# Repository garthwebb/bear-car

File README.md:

# Bear Car

Bear car is an art car project brought to Burning Man in 2015 ([photos](https://photos.app.goo.gl/hQNxJEHgqHZzFq1y2)), meant to look like
[rilakkuma](http://www.san-x.jp/characters/rilakkuma.html), the lazy bear.

It consists of two Huffy beach cruiser bikes that are bolted together.
A linkage in front connects the two bicycles steering columns in an Ackermann steering geometry.  The bicycles are driven by two 350W electric
motors via a chain to the rear wheels.  Two people can ride in the car, who's top speed is around 15mph and can drive for around 2 hours on a charge.

An LED controller connects to a WiFi router that allows an iPhone running [L.E.D Labs](https://apps.apple.com/us/app/l-e-d-lab/id832042156)
to connect and control the dome lights.

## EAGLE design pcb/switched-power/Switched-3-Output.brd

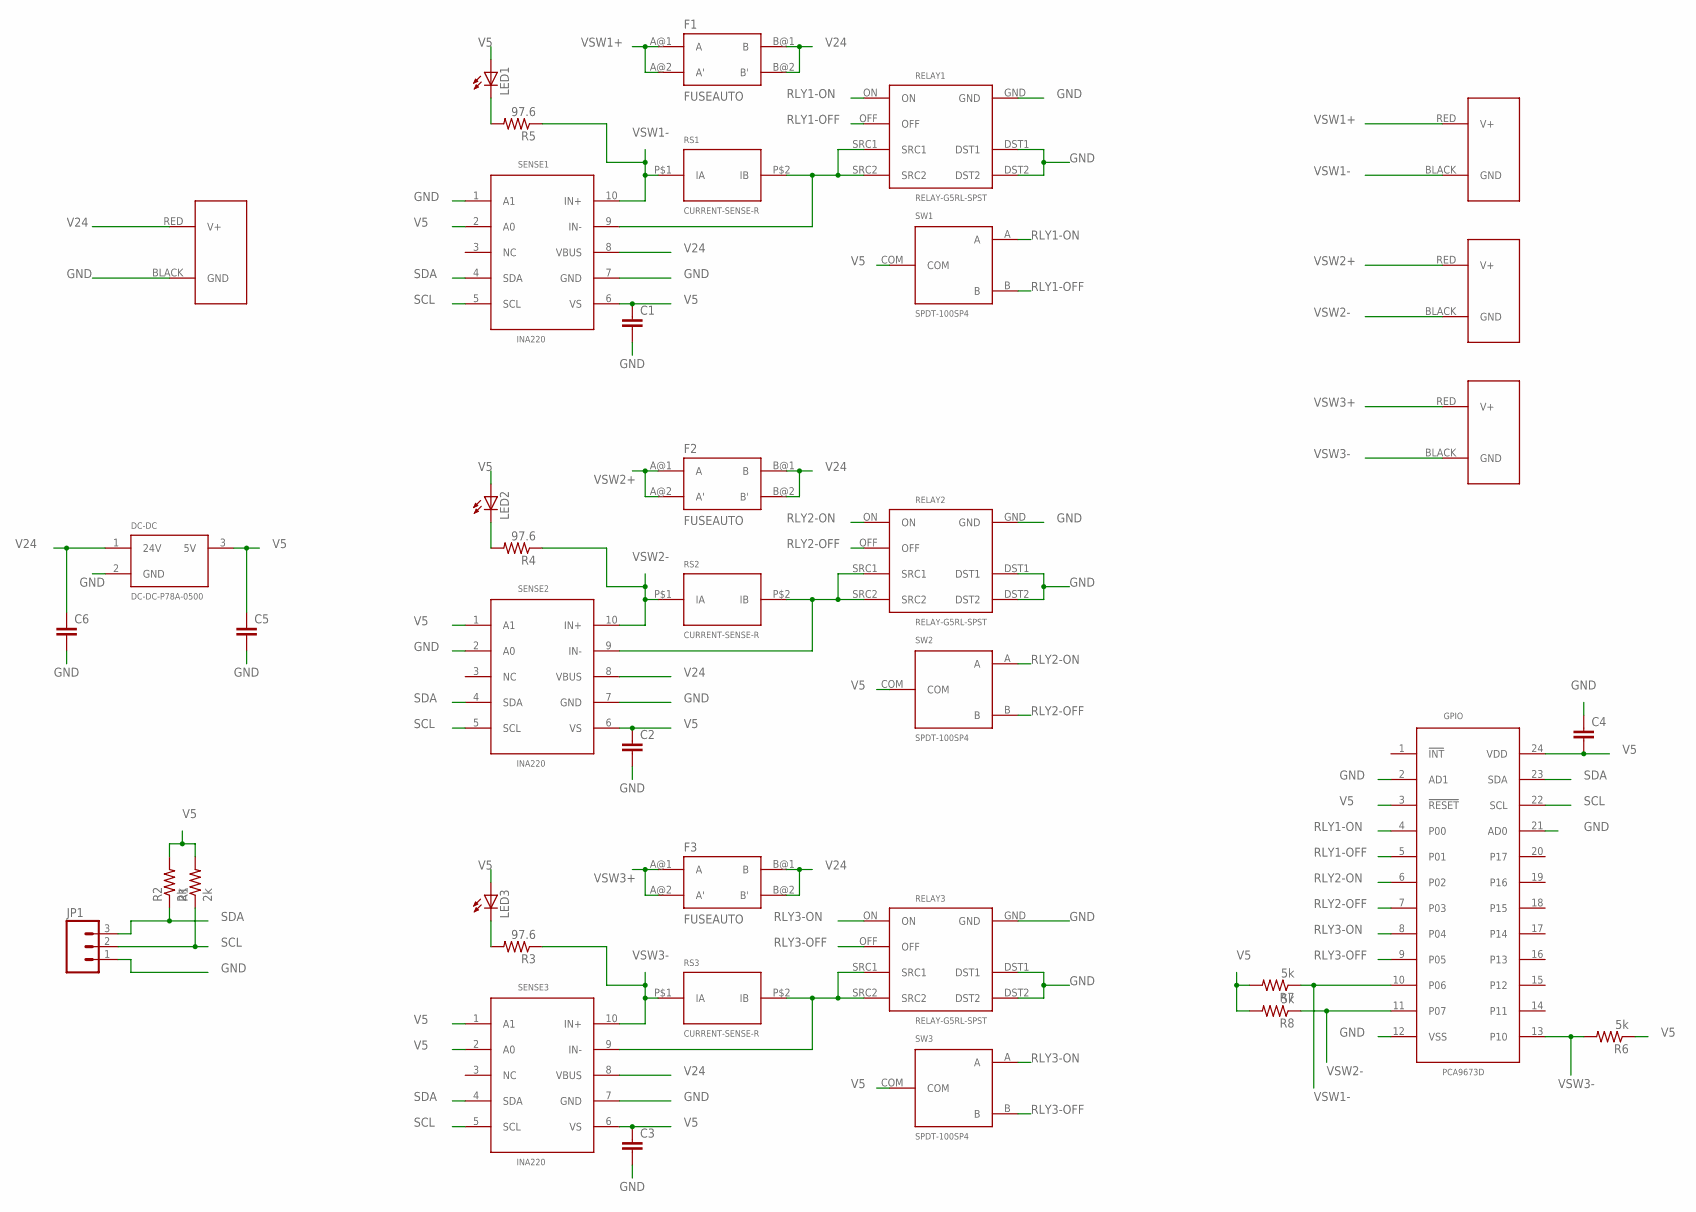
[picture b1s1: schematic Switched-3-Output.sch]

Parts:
C1, C2, C3, C4, C5, C6: C-EUC0805; C0805
DC-DC: DC-DC-P78A-0500
F1, F2, F3: FUSEAUTO; FUSE
GPIO: PCA9673D; SO24
JP1: M03PTH; 1X03
LED1, LED2, LED3: LED3MM
PWR: POWERPOLE_POWER45A_DRILL; POWERPOLE_PAIR_45A_HOLE
R1, R2: 2k; R0805
R3, R4, R5: 97.6; R0805
R6, R7, R8: 5k; R0805
RELAY1, RELAY2, RELAY3: RELAY-G5RL-SPST
RS1, RS2, RS3: CURRENT-SENSE-R
SENSE1, SENSE2, SENSE3: INA220; SOP-10
SW1, SW2, SW3: SPDT-100SP4
VSW1, VSW2, VSW3: POWERPOLE_POWER45A_DRILL; POWERPOLE_PAIR_45A_HOLE

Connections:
GND: C1.2, C2.2, C3.2, C4.1, C5.2, C6.2, DC-DC.2 (GND), GPIO.2 (AD1), GPIO.12 (VSS), GPIO.21 (AD0), JP1.1, PWR.BLACK (GND), RELAY1.DST1, RELAY1.DST2, RELAY1.GND, RELAY2.DST1, RELAY2.DST2, RELAY2.GND, RELAY3.DST1, RELAY3.DST2, RELAY3.GND, SENSE1.1 (A1), SENSE1.7 (GND), SENSE2.2 (A0), SENSE2.7 (GND), SENSE3.7 (GND)
unnamed: LED1.K (C), R5.2
unnamed: RELAY1.SRC1, RELAY1.SRC2, RS1.P$2 (IB), SENSE1.9 (IN-)
unnamed: RELAY3.SRC1, RELAY3.SRC2, RS3.P$2 (IB), SENSE3.9 (IN-)
unnamed: LED2.K (C), R4.2
unnamed: RELAY2.SRC1, RELAY2.SRC2, RS2.P$2 (IB), SENSE2.9 (IN-)
unnamed: LED3.K (C), R3.2
RLY1-OFF: GPIO.5 (P01), RELAY1.OFF, SW1.B
RLY1-ON: GPIO.4 (P00), RELAY1.ON, SW1.A
RLY2-OFF: GPIO.7 (P03), RELAY2.OFF, SW2.B
RLY2-ON: GPIO.6 (P02), RELAY2.ON, SW2.A
RLY3-OFF: GPIO.9 (P05), RELAY3.OFF, SW3.B
RLY3-ON: GPIO.8 (P04), RELAY3.ON, SW3.A
SCL: GPIO.22 (SCL), JP1.2, R1.1, SENSE1.5 (SCL), SENSE2.5 (SCL), SENSE3.5 (SCL)
SDA: GPIO.23 (SDA), JP1.3, R2.1, SENSE1.4 (SDA), SENSE2.4 (SDA), SENSE3.4 (SDA)
V5: C1.1, C2.1, C3.1, C4.2, C5.1, DC-DC.3 (5V), GPIO.3 (!RESET!), GPIO.24 (VDD), LED1.A, LED2.A, LED3.A, R1.2, R2.2, R6.1, R7.2, R8.2, SENSE1.2 (A0), SENSE1.6 (VS), SENSE2.1 (A1), SENSE2.6 (VS), SENSE3.1 (A1), SENSE3.2 (A0), SENSE3.6 (VS), SW1.COM, SW2.COM, SW3.COM
V24: C6.1, DC-DC.1 (24V), F1.B@1 (B), F1.B@2 (B'), F2.B@1 (B), F2.B@2 (B'), F3.B@1 (B), F3.B@2 (B'), PWR.RED (V+), SENSE1.8 (VBUS), SENSE2.8 (VBUS), SENSE3.8 (VBUS)
VSW1+: F1.A@1 (A), F1.A@2 (A'), VSW1.RED (V+)
VSW1-: GPIO.10 (P06), R5.1, R7.1, RS1.P$1 (IA), SENSE1.10 (IN+), VSW1.BLACK (GND)
VSW2+: F2.A@1 (A), F2.A@2 (A'), VSW2.RED (V+)
VSW2-: GPIO.11 (P07), R4.1, R8.1, RS2.P$1 (IA), SENSE2.10 (IN+), VSW2.BLACK (GND)
VSW3+: F3.A@1 (A), F3.A@2 (A'), VSW3.RED (V+)
VSW3-: GPIO.13 (P10), R3.1, R6.2, RS3.P$1 (IA), SENSE3.10 (IN+), VSW3.BLACK (GND)

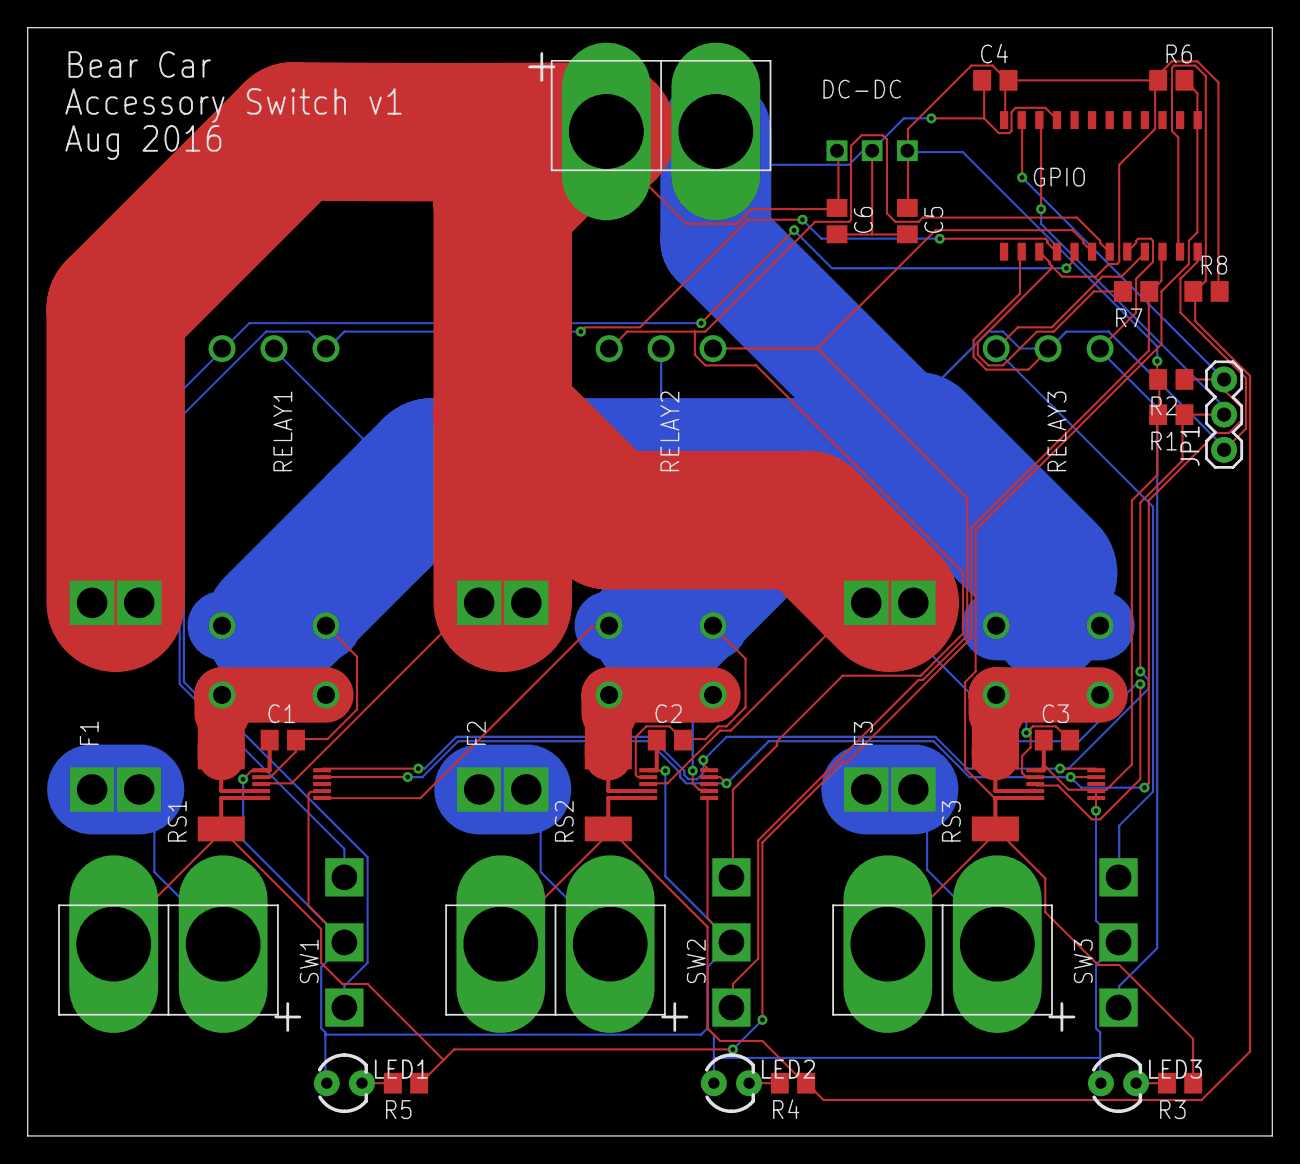
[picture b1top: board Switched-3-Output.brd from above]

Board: 2 copper layers, 89.8 x 80.0 mm, 39 parts (0 on the bottom side), 23 nets.

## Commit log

2018-11-03 Add pcb layout stuff first
2018-11-03 Add gitignore, plus make new revision with latest board
2018-11-03 Remaining design files
